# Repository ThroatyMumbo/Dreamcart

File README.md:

# The Dreamcart!

Not to be confused with the piece of furniture of the same name...

This is a set of cartridge readers for Dreamcast that supports N64, SNES, and Genesis (or Mega Drive if that's your fancy).
It can be used to play your physical game copies (complete with save data!) via an emulator or through a dynamic recompiler (for N64 only).

Video demo: https://youtu.be/mrIwJNA4yfQ

## Disclaimer

Since these readers use actual cartridges, exercise caution and **use at your own risk**.
After building the reader (or using an equivalent bench setup), always test it on a throwaway cartridge first and backup your save files if possible.
Throughout all my testing I personally haven't lost any save data *yet*, but the risk is still there.

Some existing cartridge readers and backup tools:
- [Open Source Cartridge Reader (OSCR)](https://github.com/sanni/cartreader)
- [Retrode 2](https://www.retrode.com/)
- [Epilogue SN Operator](https://epilogue.co/product/sn-operator)

## Requirements

### Hardware
- A Dreamcast (duh)
- Any of the cart readers (PCBs under [hardware/][hardware/]) + cartridges
   - For N64: This can really be any RP2350B-based MCU hooked up directly to a cartridge slot with the proper wiring. Not ideal but it does work.
- [dcload-ip](https://github.com/KallistiOS/dcload-ip) burned to a disc
- A CMSIS-DAP debug probe (e.g. Raspberry Pi Debug Probe) for loading the firmware

### Software
- [Raspberry Pi Pico SDK](https://github.com/raspberrypi/pico-sdk) for building the firmware
- [OpenOCD](https://github.com/raspberrypi/openocd) with RP2350 support for loading it
- [KallistiOS](https://github.com/KallistiOS/KallistiOS) and the built toolchain
- dc-tool-ip for loading software onto the Dreamcast (I typically use Ethernet via the BBA)
  - You could *probably* burn the software to a disc and run it directly, but I haven't tested this.

## Usage

### Firmware

Each cart reader has its own firmware under `firmware/`, sharing code from `firmware/common/`:

| Reader  | Directory           | Output        |
|---------|---------------------|---------------|
| N64     | `firmware/n64`      | `n64link.elf` |
| SNES    | `firmware/snes`     | `sneslink.elf`|
| Genesis | `firmware/genesis`  | `mdlink.elf`  |

#### Building

Needs the Pico SDK (2.x), CMake, Ninja and `arm-none-eabi-gcc`. The board type defaults to `pimoroni_pga2350`.

```sh
export PICO_SDK_PATH=/path/to/pico-sdk
cmake -S firmware/n64 -B firmware/n64/build -G Ninja
cmake --build firmware/n64/build
```

Swap `n64` for `snes` or `genesis` to build the other readers.

#### Loading

The firmware is loaded over SWD with a CMSIS-DAP probe (e.g. a Raspberry Pi Debug Probe) wired to the reader's `SWD+UART` header, using an OpenOCD build with RP2350 support:

```sh
openocd -f interface/cmsis-dap.cfg -f target/rp2350.cfg \
  -c "adapter speed 5000" \
  -c "program firmware/n64/build/n64link.elf verify reset exit"
```

Power the reader before connecting the probe. The firmware's console is on UART1 (GP40 TX / GP41 RX, 115200 baud), on the same header.

Flashing over USB via bootselect can be done as well, but SWD is typically easier and allows for repeated flashing without the bootselect song and dance (or USB becoming unresponsive, which it loves to do).

### Dreamcart 64

This assumes you're using dcload-ip for running custom Dreamcast software.

1) Run dcload-ip on your Dreamcast
2) Setup environment vars:
```sh
source /opt/toolchains/dc/kos/environ.sh # KallistiOS env
export DC_IP=192.168.*.* # Use the IP address shown on DC screen
```
3) Launch it
```sh
recomp/run.sh
```

You should see "Dreamcart 64" which auto-detects the cart reader and should display the title of the cartridge.
- Titles might be slightly off since it reads it from the cartridge header and does some formatting.
- If the title shows up as a jumbled mess or "No cartridge" then you'll have to "Swap cartridge" and reseat (the joys of cartridges!)

## FAQ

### Which games does this support?
Of the N64 games I own and have tested:

| Game | Supported? |
|------|------------|
| Super Mario 64 | Yes |
| Mario Kart 64 | Yes |
| Kirby 64 | Yes |
| Rayman 2 | Yes |
| Cruis'n USA | Yes |
| Cruis'n World | Yes |
| Elmo's Number Journey | Yes |
| THPS 2 | Yes |
| Pokémon Stadium 2 | Barely |
| Donkey Kong 64 | No |

For SNES and Genesis it's up to what the emulators support. I've tested Donkey Kong Country, Super Mario All Stars, and Mortal Kombat II (on Genesis). The only issues have been sound-related.

### Why not just use ROMs?
Besides the legally dubious nature of ROMs themselves, I like the idea of being able to access an exact copy of a game from different places,
more specifically the save data. No juggling save files around or dealing with the logistics of how to transfer a save or ROM from one place to
another. Also, using actual cartridges is cooler.

### What about games that require a save pak?
The Dreamcast VMU emulates the save pak using 66 blocks (32 KB). If you don't have room for that you'll get a warning before starting any
game (haven't figured out a clean way to check if the game actually requires one or not).

As for transferring data to/from an actual save pak, this is technically possible but not supported in this project.
- FWIW, one way to do this is to hook up an N64 controller to an MCU (potentially even the cartridge reader itself, but I haven't tested this)
  and use the Joybus PIO to read the save pak data off the controller while the save pak is inserted.
  Then you can use a custom DC program to copy that to the VMU via dcload-ip's PC link. So yeah, technically possible but very clunky.

### How do I get SNES and Genesis games working?
These require a modified version of [Super Famicast](https://github.com/sega-dreamcast/super-famicast) and/or [Genesis Plus DC](https://github.com/nextgeniuspro/genesisplus-dc).
Still working on adding a clean set of patches to this repo to support the cartridge reader stuff.

I don't plan on adding a native recompiler for these platforms. N64 is the main focus.

### What's the SD card for?
This is an optional large size cache for recompiled games from the Dreamcart 64 to reduce boot times. The PGA2350's 16 MB cache could be used as well, but obviously that fills up fast.
It's currently not used for anything on the SNES and Genesis readers.

## Credits and References

### Firmware

- **[Open Source Cartridge Reader (OSCR)](https://github.com/sanni/cartreader)**: The main reference for the core cartridge reader firmware.
- **[MaplePad](https://github.com/mackieks/MaplePad)**: Core Dreamcast controller protocol (Maple Bus) code that I've used successfully in several projects.
- **[no-OS-FatFS-SD-SDIO-SPI-RPi-Pico](https://github.com/carlk3/no-OS-FatFS-SD-SDIO-SPI-RPi-Pico)**: Used for the optional SD card recompiled game cache

### N64 Recompiler

- **[N64Recomp](https://github.com/N64Recomp/N64Recomp)**: The main reference for the recompiler. Would not be feasible otherwise.
- **[rabbitizer](https://github.com/Decompollaborate/rabbitizer)** (MIT): MIPS decoder, vendored in `recomp/rabbitizer`
- **[mupen64plus-rsp-hle](https://github.com/mupen64plus/mupen64plus-rsp-hle)** (GPLv2): audio microcode primitives, vendored in `recomp/mupen64plus-rsp-hle`
- **[DaedalusX64](https://github.com/DaedalusX64/daedalus)**: libultra function signatures (`hooks/patch_symbols.inl`)
- **[ultralib](https://github.com/decompals/ultralib)**: libgultra signatures (`hooks/libgultra.inl`)
- **[ares](https://github.com/ares-emulator/ares)**: reference for PIF and Controller Pak behavior
- **[f3dex2](https://github.com/Mr-Wiseguy/f3dex2)**: F3DEX2 microcode reference
- **[LZ4](https://github.com/lz4/lz4)**: block format used for the translation cache
- **[dcload-ip](https://github.com/KallistiOS/dcload-ip)**: loading and console I/O over the BBA

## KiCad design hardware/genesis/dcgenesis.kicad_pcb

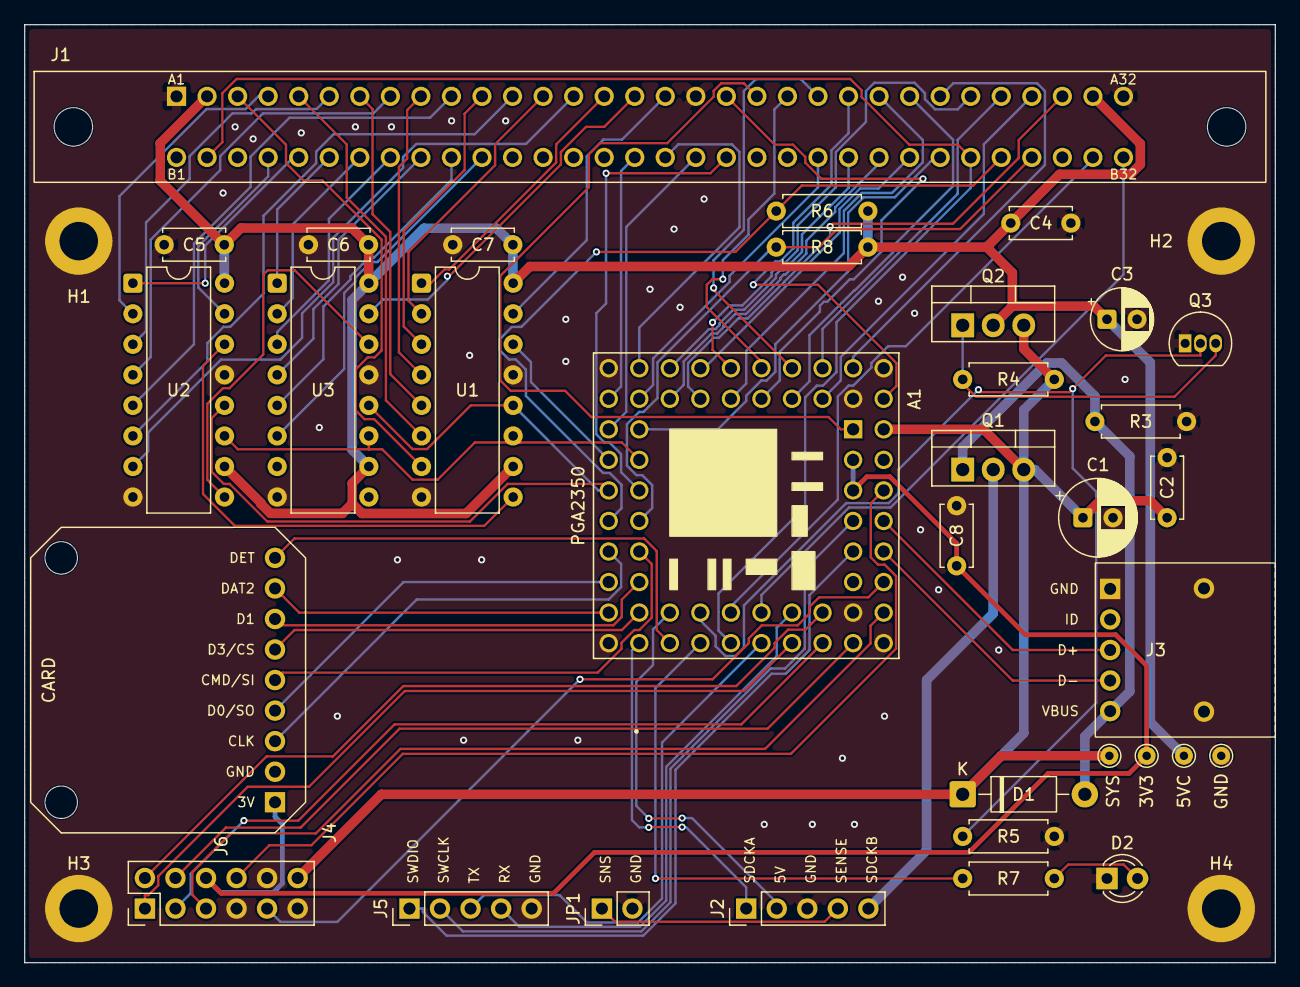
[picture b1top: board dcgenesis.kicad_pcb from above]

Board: 2 copper layers, 104.0 x 78.0 mm, 38 parts (0 on the bottom side), 87 nets.

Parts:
3V3: +3V3; TestPoint_THTPad_D1.5mm_Drill0.7mm
5VC: CART_5V; TestPoint_THTPad_D1.5mm_Drill0.7mm
A1: PGA2350; Pimoroni_PGA2350
C1: 100u/16V; CP_Radial_D6.3mm_P2.50mm
C2, C4, C5, C6, C7, C8: 100n; C_Disc_D5.0mm_W2.5mm_P5.00mm
C3: 10u/16V; CP_Radial_D5.0mm_P2.50mm
D1: 1N5817; D_DO-41_SOD81_P10.16mm_Horizontal
D2: LED 3mm; LED_D3.0mm
GND: GND; TestPoint_THTPad_D1.5mm_Drill0.7mm
H1, H2, H3, H4: M3; MountingHole_3.2mm_M3_DIN965_Pad
J1: GENESIS CART SLOT; Genesis_Cart_Slot_2x32_P2.54mm
J2: MAPLE; PinHeader_1x05_P2.54mm_Vertical
J3: USB DEVICE; USB_Micro_DIP_1x05_P2.54mm
J4: MICROSD 4682; Adafruit_4682_microSD
J5: SWD+UART; PinHeader_1x05_P2.54mm_Vertical
J6: SPARE GPIO; PinHeader_2x06_P2.54mm_Vertical
JP1: SENSE-GND; PinHeader_1x02_P2.54mm_Vertical
Q1, Q2: NDP6020P; TO-220-3_Vertical
Q3: 2N7000; TO-92_Inline
R3: 100k; R_Axial_DIN0207_L6.3mm_D2.5mm_P7.62mm_Horizontal
R4, R5, R6, R8: 10k; R_Axial_DIN0207_L6.3mm_D2.5mm_P7.62mm_Horizontal
R7: 1k; R_Axial_DIN0207_L6.3mm_D2.5mm_P7.62mm_Horizontal
SYS: +5V_SYS; TestPoint_THTPad_D1.5mm_Drill0.7mm
U1, U2, U3: 74HCT595; DIP-16_W7.62mm

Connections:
/+3V3: 3V3.1 (1_1), A1.53 (ADC_VREF), A1.55 (3V3), C8.1, J4.1 (3V), J6.6
/+5V_SYS: A1.57 (VBUS), C1.1, C2.1, D1.1 (K), J6.12, Q1.3 (S), Q2.3 (S), R4.1, SYS.1 (1_1)
/ADDR_Q12: U1.9 (QH'), U2.14 (SER)
/ADDR_Q23: U2.9 (QH'), U3.14 (SER)
/ADDR_RCLK: A1.22 (GPIO22), U1.12 (RCLK), U2.12 (RCLK), U3.12 (RCLK)
/ADDR_SER: A1.20 (GPIO20), U1.14 (SER)
/ADDR_SRCLK: A1.21 (GPIO21), U1.11 (SRCLK), U2.11 (SRCLK), U3.11 (SRCLK)
/ASEL_N: A1.19 (GPIO19), J1.B26 (/ASEL)
/AS_N: A1.18 (GPIO18), J1.B18 (/AS)
/BOOTSEL: A1.48 (BOOTSEL), J6.9
/CART_5V: 5VC.1 (1_1), C3.1, C4.1, C5.1, C6.1, C7.1, J1.A2 (VCC), J1.A31 (VCC), Q2.2 (D), R6.2, R8.2, U1.10 (~SRCLR), U1.16 (VCC), U2.10 (~SRCLR), U2.16 (VCC), U3.10 (~SRCLR), U3.16 (VCC)
/CART_DET: A1.39 (GPIO39), J1.B32 (/CART)
/CART_GATE: Q2.1 (G), Q3.3 (D), R4.2
/CART_PWR_EN: A1.35 (GPIO35), Q3.2 (G), R5.1
/CART_RESET_N: A1.38 (GPIO38), J1.B2 (/MRES), J1.B27 (/VRES)
/CE_N: A1.16 (GPIO16), J1.B17 (/CE0)
/GND: A1.58 (GND), A1.59 (GND), A1.60 (GND), A1.61 (GND), A1.62 (GND), A1.63 (GND), C1.2, C2.2, C3.2, C4.2, C5.2, C6.2, C7.2, C8.2, D2.1 (K), GND.1 (1_1), H1.1 (1_1), H2.1 (1_1), H3.1 (1_1), H4.1 (1_1), J1.A1 (GND), J1.A18 (GND), J1.A32 (GND), J2.3, J3.1 (GND), J3.SH (SHIELD), J4.2 (GND), J5.5, J6.7, J6.10, J6.11, JP1.2, Q3.1 (S), R3.2, R5.2, U1.8 (GND), U1.13 (~OE), U2.8 (GND), U2.13 (~OE), U3.8 (GND), U3.13 (~OE)
/GP42: A1.42 (GPIO42), J6.1
/GP43: A1.43 (GPIO43), J6.2
/GP44: A1.44 (GPIO44), J6.3
/GP45: A1.45 (GPIO45), J6.4
/GP46: A1.46 (GPIO46), J6.5
/LED: A1.36 (GPIO36), R7.1
/LED_A: D2.2 (A), R7.2
/LWR_N: A1.24 (GPIO24), J1.B28 (/LWR), R6.1
/MAPLE_5V: J2.5, Q1.2 (D)
/MAPLE_SENSE: J2.4, JP1.1
/OE_N: A1.17 (GPIO17), J1.B16 (/CAS0)
/RUN: A1.54 (RUN), J6.8
/SDCKA: A1.32 (GPIO32), J2.1
/SDCKB: A1.33 (GPIO33), J2.2
/SD_CLK: A1.26 (GPIO26), J4.3 (CLK)
/SD_CMD: A1.27 (GPIO27), J4.5 (CMD/SI)
/SD_D0: A1.28 (GPIO28), J4.4 (D0/SO)
/SD_D1: A1.29 (GPIO29), J4.7 (D1)
/SD_D2: A1.30 (GPIO30), J4.8 (DAT2)
/SD_D3: A1.31 (GPIO31), J4.6 (D3/CS)
/SD_DET: A1.34 (GPIO34), J4.9 (DET)
/SWCLK: A1.51 (SWCLK), J5.2
/SWDIO: A1.49 (SWDIO), J5.1
/TIME_N: A1.37 (GPIO37), J1.B31 (/TIME)
/UART_RX: A1.41 (GPIO41), J5.4
/UART_TX: A1.40 (GPIO40), J5.3
/USB_DM: A1.50 (USB_DM), J3.4 (D-)
/USB_DP: A1.52 (USB_DP), J3.3 (D+)
/UWR_N: A1.25 (GPIO25), J1.B29 (/UWR), R8.1
/VA1: J1.A17 (VA1), U1.15 (QA)
/VA2: J1.A15 (VA2), U1.1 (QB)
/VA3: J1.A13 (VA3), U1.2 (QC)
/VA4: J1.A11 (VA4), U1.3 (QD)
/VA5: J1.A9 (VA5), U1.4 (QE)
/VA6: J1.A7 (VA6), U1.5 (QF)
/VA7: J1.A5 (VA7), U1.6 (QG)
/VA8: J1.A3 (VA8), U1.7 (QH)
/VA9: J1.B4 (VA9), U2.15 (QA)
/VA10: J1.B5 (VA10), U2.1 (QB)
/VA11: J1.A4 (VA11), U2.2 (QC)
/VA12: J1.A6 (VA12), U2.3 (QD)
/VA13: J1.A8 (VA13), U2.4 (QE)
/VA14: J1.A10 (VA14), U2.5 (QF)
/VA15: J1.A12 (VA15), U2.6 (QG)
/VA16: J1.A14 (VA16), U2.7 (QH)
/VA17: J1.A16 (VA17), U3.15 (QA)
/VA18: J1.B6 (VA18), U3.1 (QB)
/VA19: J1.B7 (VA19), U3.2 (QC)
/VA20: J1.B8 (VA20), U3.3 (QD)
/VA21: J1.B9 (VA21), U3.4 (QE)
/VA22: J1.B10 (VA22), U3.5 (QF)
/VA23: J1.B11 (VA23), U3.6 (QG)
/VBUS: D1.2 (A), J3.5 (VBUS), Q1.1 (G), R3.1
/VCLK: A1.23 (GPIO23), J1.B19 (VCLK)
/VD0: A1.0 (GPIO0), J1.A20 (VD0)
/VD1: A1.1 (GPIO1), J1.A23 (VD1)
/VD2: A1.2 (GPIO2), J1.A26 (VD2)
/VD3: A1.3 (GPIO3), J1.A29 (VD3)
/VD4: A1.4 (GPIO4), J1.A28 (VD4)
/VD5: A1.5 (GPIO5), J1.A25 (VD5)
/VD6: A1.6 (GPIO6), J1.A22 (VD6)
/VD7: A1.7 (GPIO7), J1.A19 (VD7)
/VD8: A1.8 (GPIO8), J1.A21 (VD8)
/VD9: A1.9 (GPIO9), J1.A24 (VD9)
/VD10: A1.10 (GPIO10), J1.A27 (VD10)
/VD11: A1.11 (GPIO11), J1.A30 (VD11)
/VD12: A1.12 (GPIO12), J1.B25 (VD12)
/VD13: A1.13 (GPIO13), J1.B24 (VD13)
/VD14: A1.14 (GPIO14), J1.B23 (VD14)
/VD15: A1.15 (GPIO15), J1.B22 (VD15)

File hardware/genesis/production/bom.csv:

Designator,Footprint,Quantity,Value,LCSC Part #
A1,Pimoroni_PGA2350,1,PGA2350,
C1,CP_Radial_D6.3mm_P2.50mm,1,100u/16V,
"C2, C4, C5, C6, C7, C8",C_Disc_D5.0mm_W2.5mm_P5.00mm,6,100n,
C3,CP_Radial_D5.0mm_P2.50mm,1,10u/16V,
D1,D_DO-41_SOD81_P10.16mm_Horizontal,1,1N5817,
D2,LED_D3.0mm,1,LED 3mm,
J1,Genesis_Cart_Slot_2x32_P2.54mm,1,GENESIS CART SLOT,
J2,PinHeader_1x05_P2.54mm_Vertical,1,MAPLE,
J3,USB_Micro_DIP_1x05_P2.54mm,1,USB DEVICE,
J4,Adafruit_4682_microSD,1,MICROSD 4682,
J5,PinHeader_1x05_P2.54mm_Vertical,1,SWD+UART,
J6,PinHeader_2x06_P2.54mm_Vertical,1,SPARE GPIO,
JP1,PinHeader_1x02_P2.54mm_Vertical,1,SENSE-GND,
"Q1, Q2",TO-220-3_Vertical,2,NDP6020P,
Q3,TO-92_Inline,1,2N7000,
R3,R_Axial_DIN0207_L6.3mm_D2.5mm_P7.62mm_Horizontal,1,100k,
"R4, R5, R6, R8",R_Axial_DIN0207_L6.3mm_D2.5mm_P7.62mm_Horizontal,4,10k,
R7,R_Axial_DIN0207_L6.3mm_D2.5mm_P7.62mm_Horizontal,1,1k,
"U1, U2, U3",DIP-16_W7.62mm,3,74HCT595,

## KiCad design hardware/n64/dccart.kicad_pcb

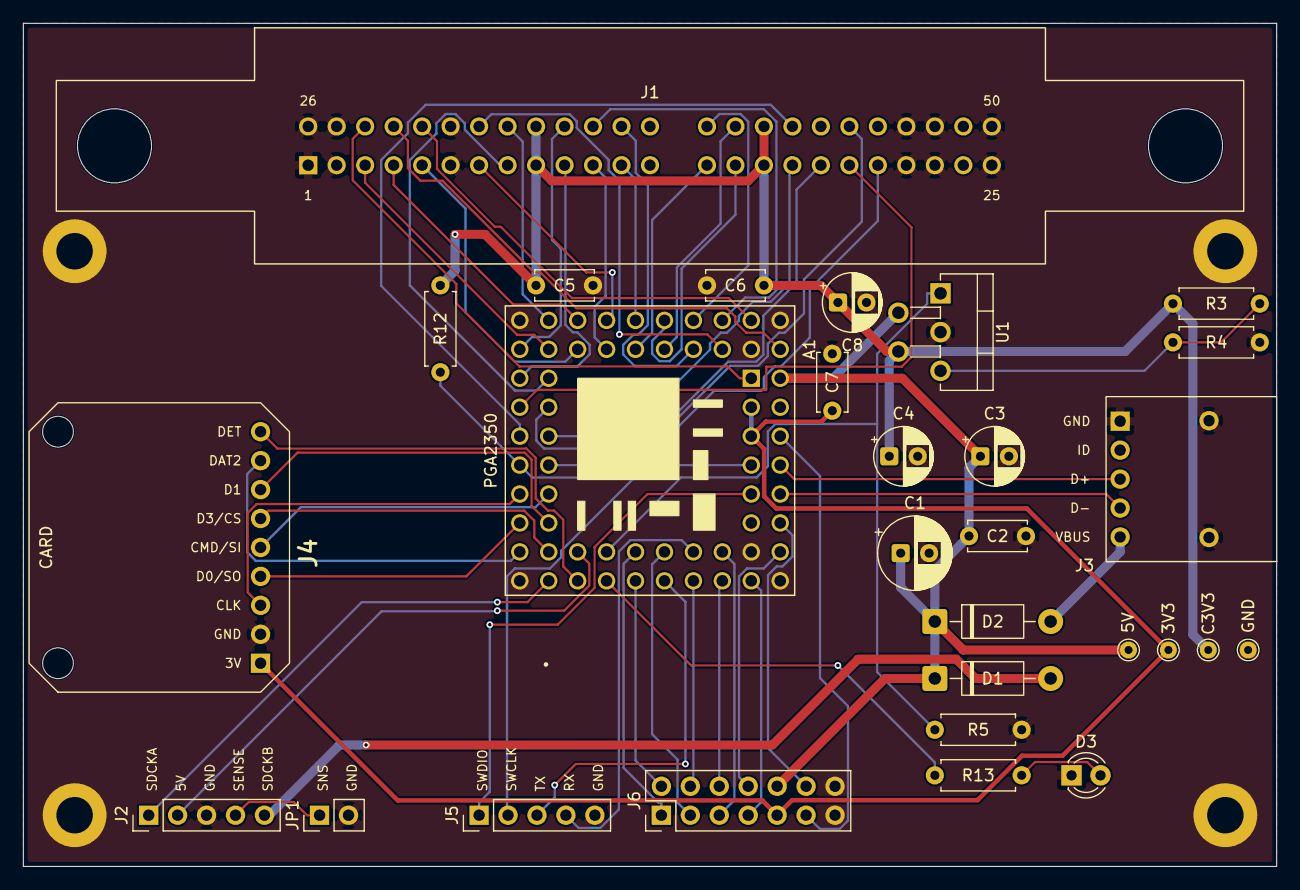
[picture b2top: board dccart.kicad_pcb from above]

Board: 2 copper layers, 110.0 x 74.0 mm, 33 parts (0 on the bottom side), 62 nets.

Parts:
3V3: +3V3; TestPoint_THTPad_D1.5mm_Drill0.7mm
5V: +5V_SYS; TestPoint_THTPad_D1.5mm_Drill0.7mm
A1: PGA2350; Pimoroni_PGA2350
C1: 100u/16V; CP_Radial_D6.3mm_P2.50mm
C2, C5, C6, C7: 100n; C_Disc_D5.0mm_W2.5mm_P5.00mm
C3, C8: 10u/16V; CP_Radial_D5.0mm_P2.50mm
C3V3: CART_3V3; TestPoint_THTPad_D1.5mm_Drill0.7mm
C4: 22u/10V; CP_Radial_D5.0mm_P2.50mm
D1, D2: 1N5817; D_DO-41_SOD81_P10.16mm_Horizontal
D3: LED 3mm; LED_D3.0mm
GND: GND; TestPoint_THTPad_D1.5mm_Drill0.7mm
H1, H2, H3, H4: M3; MountingHole_3.2mm_M3_DIN965_Pad
J1: N64 CART SLOT; N64_Cart_Slot_2x25_P2.50mm
J2: MAPLE; PinHeader_1x05_P2.54mm_Vertical
J3: USB DEVICE; USB_Micro_DIP_1x05_P2.54mm
J4: MICROSD 4682; Adafruit_4682_microSD
J5: SWD+UART; PinHeader_1x05_P2.54mm_Vertical
J6: SPARE GPIO; PinHeader_2x07_P2.54mm_Vertical
JP1: SENSE-GND; PinHeader_1x02_P2.54mm_Vertical
R3: 402 1%; R_Axial_DIN0207_L6.3mm_D2.5mm_P7.62mm_Horizontal
R4: 240 1%; R_Axial_DIN0207_L6.3mm_D2.5mm_P7.62mm_Horizontal
R5: 10k; R_Axial_DIN0207_L6.3mm_D2.5mm_P7.62mm_Horizontal
R12: 4.7k; R_Axial_DIN0207_L6.3mm_D2.5mm_P7.62mm_Horizontal
R13: 1k; R_Axial_DIN0207_L6.3mm_D2.5mm_P7.62mm_Horizontal
U1: MIC29152WT; TO-220-5_P3.4x3.7mm_StaggerEven_Lead3.8mm_Vertical

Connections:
/+3V3: 3V3.1 (1_1), A1.53 (ADC_VREF), A1.55 (3V3), C7.1, J4.1 (3V), J6.9
/+5V_SYS: 5V.1 (1_1), A1.57 (VBUS), C1.1, C2.1, C3.1, D1.1 (K), D2.1 (K), J6.10, U1.2 (VIN)
/AD0: A1.0 (GPIO0), J1.28 (AD0)
/AD1: A1.1 (GPIO1), J1.29 (AD1)
/AD2: A1.2 (GPIO2), J1.30 (AD2)
/AD3: A1.3 (GPIO3), J1.32 (AD3)
/AD4: A1.4 (GPIO4), J1.36 (AD4)
/AD5: A1.5 (GPIO5), J1.37 (AD5)
/AD6: A1.6 (GPIO6), J1.40 (AD6)
/AD7: A1.7 (GPIO7), J1.41 (AD7)
/AD8: A1.8 (GPIO8), J1.16 (AD8)
/AD9: A1.9 (GPIO9), J1.15 (AD9)
/AD10: A1.10 (GPIO10), J1.12 (AD10)
/AD11: A1.11 (GPIO11), J1.11 (AD11)
/AD12: A1.12 (GPIO12), J1.7 (AD12)
/AD13: A1.13 (GPIO13), J1.5 (AD13)
/AD14: A1.14 (GPIO14), J1.4 (AD14)
/AD15: A1.15 (GPIO15), J1.3 (AD15)
/ALE_H: A1.17 (GPIO17), J1.35 (ALE_H)
/ALE_L: A1.16 (GPIO16), J1.33 (ALE_L)
/BOOTSEL: A1.48 (BOOTSEL), J6.12
/CART_3V3: C3V3.1 (1_1), C4.1, C5.1, C6.1, C8.1, J1.9 (VCC), J1.17 (VCC), J1.34 (VCC), J1.42 (VCC), R3.1, R12.2, U1.4 (VOUT)
/CART_ADJ: R3.2, R4.1, U1.5 (ADJ)
/CART_NMI: A1.25 (GPIO25), J1.45 (NMI)
/CART_PWR_EN: A1.35 (GPIO35), R5.1, U1.1 (EN)
/CART_RESET_N: A1.20 (GPIO20), J1.20 (/RESET)
/CIC_CLK: A1.21 (GPIO21), J1.19 (CIC_CLK)
/CIC_DCLK: A1.22 (GPIO22), J1.43 (PIF_TO_CIC)
/CIC_DIO: A1.23 (GPIO23), J1.18 (CIC_TO_PIF)
/GND: A1.58 (GND), A1.59 (GND), A1.60 (GND), A1.61 (GND), A1.62 (GND), A1.63 (GND), C1.2, C2.2, C3.2, C4.2, C5.2, C6.2, C7.2, C8.2, D3.1 (K), GND.1 (1_1), H1.1 (1_1), H2.1 (1_1), H3.1 (1_1), H4.1 (1_1), J1.1 (GND), J1.2 (GND), J1.6 (GND), J1.22 (GND), J1.23 (GND), J1.25 (GND), J1.26 (GND), J1.27 (GND), J1.31 (GND), J1.47 (GND), J1.48 (GND), J1.50 (GND), J2.3, J3.1 (GND), J3.SH (SHIELD), J4.2 (GND), J5.5, J6.13, J6.14, JP1.2, R4.2, R5.2, U1.3 (GND)
/GP37: A1.37 (GPIO37), J6.1
/GP38: A1.38 (GPIO38), J6.2
/GP39: A1.39 (GPIO39), J6.3
/GP42: A1.42 (GPIO42), J6.4
/GP43: A1.43 (GPIO43), J6.5
/GP44: A1.44 (GPIO44), J6.6
/GP45: A1.45 (GPIO45), J6.7
/GP46: A1.46 (GPIO46), J6.8
/LED: A1.36 (GPIO36), R13.1
/LED_A: D3.2 (A), R13.2
/MAPLE_5V: D1.2 (A), J2.5
/MAPLE_SENSE: J2.4, JP1.1
/RD_N: A1.18 (GPIO18), J1.10 (/READ)
/RUN: A1.54 (RUN), J6.11
/SDCKA: A1.32 (GPIO32), J2.1
/SDCKB: A1.33 (GPIO33), J2.2
/SD_CLK: A1.26 (GPIO26), J4.3 (CLK)
/SD_CMD: A1.27 (GPIO27), J4.5 (CMD/SI)
/SD_D0: A1.28 (GPIO28), J4.4 (D0/SO)
/SD_D1: A1.29 (GPIO29), J4.7 (D1)
/SD_D2: A1.30 (GPIO30), J4.8 (DAT2)
/SD_D3: A1.31 (GPIO31), J4.6 (D3/CS)
/SD_DET: A1.34 (GPIO34), J4.9 (DET)
/SWCLK: A1.51 (SWCLK), J5.2
/SWDIO: A1.49 (SWDIO), J5.1
/S_DAT: A1.24 (GPIO24), J1.21 (S_DAT), R12.1
/UART_RX: A1.41 (GPIO41), J5.4
/UART_TX: A1.40 (GPIO40), J5.3
/USB_DM: A1.50 (USB_DM), J3.4 (D-)
/USB_DP: A1.52 (USB_DP), J3.3 (D+)
/VBUS: D2.2 (A), J3.5 (VBUS)
/WR_N: A1.19 (GPIO19), J1.8 (/WRITE)

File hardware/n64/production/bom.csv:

Designator,Footprint,Quantity,Value,LCSC Part #
A1,Pimoroni_PGA2350,1,PGA2350,
C1,CP_Radial_D6.3mm_P2.50mm,1,100u/16V,
"C2, C5, C6, C7",C_Disc_D5.0mm_W2.5mm_P5.00mm,4,100n,
"C3, C8",CP_Radial_D5.0mm_P2.50mm,2,10u/16V,
C4,CP_Radial_D5.0mm_P2.50mm,1,22u/10V,
"D1, D2",D_DO-41_SOD81_P10.16mm_Horizontal,2,1N5817,
D3,LED_D3.0mm,1,LED 3mm,
J1,N64_Cart_Slot_2x25_P2.50mm,1,N64 CART SLOT,
J2,PinHeader_1x05_P2.54mm_Vertical,1,MAPLE,
J3,USB_Micro_DIP_1x05_P2.54mm,1,USB DEVICE,
J4,Adafruit_4682_microSD,1,MICROSD 4682,
J5,PinHeader_1x05_P2.54mm_Vertical,1,SWD+UART,
J6,PinHeader_2x07_P2.54mm_Vertical,1,SPARE GPIO,
JP1,PinHeader_1x02_P2.54mm_Vertical,1,SENSE-GND,
R12,R_Axial_DIN0207_L6.3mm_D2.5mm_P7.62mm_Horizontal,1,4.7k,
R13,R_Axial_DIN0207_L6.3mm_D2.5mm_P7.62mm_Horizontal,1,1k,
R3,R_Axial_DIN0207_L6.3mm_D2.5mm_P7.62mm_Horizontal,1,402 1%,
R4,R_Axial_DIN0207_L6.3mm_D2.5mm_P7.62mm_Horizontal,1,240 1%,
R5,R_Axial_DIN0207_L6.3mm_D2.5mm_P7.62mm_Horizontal,1,10k,
U1,TO-220-5_P3.4x3.7mm_StaggerEven_Lead3.8mm_Vertical,1,MIC29152WT,

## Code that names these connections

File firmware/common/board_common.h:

// What every cart reader board shares: PGA2350, Maple on GP32/GP33, UART1 console on GP40/GP41 (set in dccart_common.cmake).
#pragma once

#define PIN_CART_PWR_EN 35      // U1 EN; R5 holds it low
#define PIN_LED         36

#define PIN_MAPLE_SDCKA 32      // SDCKB must be the next pin up
#define PIN_MAPLE_SDCKB 33
#define PIO_MAPLE       pio2    // claimed whole by dc_link

#define PIN_SD_CLK      26      // SPI1 SCK
#define PIN_SD_CMD      27      // SPI1 TX
#define PIN_SD_D0       28      // SPI1 RX
#define PIN_SD_D3       31      // CS in SPI mode
#define PIN_SD_DET      34      // high = card in the slot
#define SD_SPI          spi1
#define PIO_SD          pio1    // SDIO; on N64 time-shared with the joybus EEPROM link

#define SYS_CLOCK_KHZ   200000  // below 200 MHz the Maple decoder stalls and drops block reads

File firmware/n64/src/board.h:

// N64 cart reader on a PGA2350; nets and cart pins in docs/board.md.
#pragma once
#include "hardware/pio.h"
#include "board_common.h"

#define AD_BASE      0      // AD0-15 on GP0-15
#define PIN_ALE_L    16     // ALE_L, ALE_H, /RD, /WR: one consecutive group for n64_bus.pio
#define PIN_ALE_H    17
#define PIN_RD       18
#define PIN_WR       19
#define PIN_RESET    20
#define PIN_CIC_CLK  21     // cart 19, ~1.95 MHz to the CIC and the EEPROM
#define PIN_CIC_DCLK 22     // cart 43, PIF -> CIC
#define PIN_CIC_DIO  23     // cart 18, CIC -> PIF
#define PIN_S_DAT    24     // cart 21, joybus to the save EEPROM
#define PIN_CART_LAST 25    // CART_NMI, cart 45, never driven; GP0-25 are every cart line

#define PIO_CART_BUS pio0
#define PIO_JOYBUS   pio1   // time-shared with SDIO (pio_share.h); the CIC reader takes it for a capture
// pio2 is Maple's, claimed whole by dc_link

#define CART_ROM     0x10000000u
#define CART_SAVE    0x08000000u
#define FRAM_CMD     0x08010000u

// Who owns which PSRAM bytes
#define PSRAM_PASS_STARTS 0x00000000u   // the whole-ROM pass: its jr ra starts, 512 KB
#define PSRAM_XC_INDEX    0x00080000u   // SD translation cache: the card's index, mirrored, 128 KB
#define PSRAM_XC_STAGE    0x000A0000u   // SD translation cache: the entry in flight, to the end of PSRAM

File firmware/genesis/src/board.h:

// Mega Drive cart reader on a PGA2350; nets and cart pins in docs/genesis_board.md.
#pragma once
#include "hardware/pio.h"
#include "board_common.h"

#define PIN_VD0         0       // VD0-15 on GP0-15
#define PIN_CE          16      // /CE0, /OE (CAS0), /AS, /ASEL: one set group for md_bus.pio
#define PIN_OE          17
#define PIN_AS          18
#define PIN_ASEL        19
#define PIN_ADDR_SER    20      // SER, SRCLK, RCLK: consecutive for md_bus.pio
#define PIN_ADDR_SRCLK  21
#define PIN_ADDR_RCLK   22
#define PIN_VCLK        23      // GPOUT1
#define PIN_LWR         24
#define PIN_UWR         25
#define PIN_CART_LAST   25

#define PIN_TIME        37      // outside pio0's window, so a static SIO select
#define PIN_CART_RESET  38      // VRES and MRES
#define PIN_CART_DET    39

#define PIO_CART_BUS    pio0
// pio1 is free; pio2 is Maple's, claimed whole by dc_link
